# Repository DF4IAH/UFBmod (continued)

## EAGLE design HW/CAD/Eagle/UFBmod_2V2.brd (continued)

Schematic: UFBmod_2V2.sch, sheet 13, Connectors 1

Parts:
C1311: 1nF; C0402
C1321, C1381: 100nF; C0402
PF1311: 1.1A/2.2A; M1206
R1311: 330kR; R0402
R1321, R1331: 1kR; R0402
R1332, R1333, R1334, R1335, R1337, R1339, R1351, R1352, R1353, R1354, R1355, R1356, R1357, R1358, R1361, R1362, R1363, R1364, R1365, R1366: 100R; R0402
R1338: 10kR; R0402
R1381: 0R; R0402
R1382, R1383: NC; R0402
S1321: KSR223G_SMD_1POL
TP1371: TPB1,27; B1,27
X1311: MOLEX 105017-0001; USB-B-MICRO-SMD_MOLEX-105017-0001
X1331: XILINX-JTAG-14; 2X07_2MM00_SHROUDED_XILINX_JTAG
X1332: HEADER-1X2; 1X02
X1351, X1361: PHOENIX_1990067_1X8X2MM50_PTSA-0-5

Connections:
+2V5: R1382.2; also elsewhere on the board
+3V3: X1332.1; also elsewhere on the board
+5V_USB: PF1311.1; also elsewhere on the board
B2W_51: R1351.2, X1351.1
B2W_52: R1352.2, X1351.2
B2W_53: R1353.2, X1351.3
B2W_54: R1354.2, X1351.4
B2W_55: R1355.2, X1351.5
B2W_56: R1356.2, X1351.6
B2W_57: R1357.2, X1351.7
B2W_58: R1358.2, X1351.8
B2W_61: R1361.2, X1361.1
B2W_62: R1362.2, X1361.2
B2W_63: R1363.2, X1361.3
B2W_64: R1364.2, X1361.4
B2W_65: R1365.2, X1361.5
B2W_66: R1366.2, X1361.6
DDR3_INIT_CALIB_COMPLETE: TP1371.TP; also elsewhere on the board
FPGA_B16_L7_N: R1364.1; also elsewhere on the board
FPGA_B16_L7_P: R1363.1; also elsewhere on the board
FPGA_B16_L9_N: R1362.1; also elsewhere on the board
FPGA_B16_L9_P: R1361.1; also elsewhere on the board
FPGA_B16_L11_N: R1366.1; also elsewhere on the board
FPGA_B16_L11_P: R1365.1; also elsewhere on the board
FPGA_B16_L16_N: R1352.1; also elsewhere on the board
FPGA_B16_L16_P: R1351.1; also elsewhere on the board
FPGA_B16_L17_N: R1356.1; also elsewhere on the board
FPGA_B16_L17_P: R1355.1; also elsewhere on the board
FPGA_B16_L18_N: R1358.1; also elsewhere on the board
FPGA_B16_L18_P: R1357.1; also elsewhere on the board
FPGA_B16_L19_N: R1354.1; also elsewhere on the board
FPGA_B16_L19_P: R1353.1; also elsewhere on the board
FPGA_JTAGEN: R1339.2; also elsewhere on the board
FPGA_RESET: C1321.2, R1321.1; also elsewhere on the board
FPGA_RESET_R: R1321.2, S1321.1
FPGA_SRST: R1337.2; also elsewhere on the board
FPGA_TCK: R1333.2; also elsewhere on the board
FPGA_TDI: R1335.2; also elsewhere on the board
FPGA_TDO: R1334.2; also elsewhere on the board
FPGA_TMS: R1332.2; also elsewhere on the board
GND: C1311.1, C1321.1, C1381.1, R1311.1, R1338.2, X1311.GND, X1331.1, X1331.3, X1331.5, X1331.7, X1331.9, X1331.11, X1331.13, X1361.8; also elsewhere on the board
JC_SRST: R1337.1, X1331.14
JC_TCK: R1333.1, X1331.6
JC_TDI: R1335.1, X1331.10
JC_TDO: R1334.1, X1331.8
JC_TMS: R1332.1, X1331.4
JC_VCCO_0: R1331.1, X1331.2
JTAG_CPLD_EN: R1338.1, R1339.1, X1332.2
U1V8: R1383.2; also elsewhere on the board
U3V3: R1381.2; also elsewhere on the board
U3V3_JTAGREF: R1331.2; also elsewhere on the board
USB_D_N: X1311.D- (J_D-); also elsewhere on the board
USB_D_P: X1311.D+ (J_D+); also elsewhere on the board
USB_ID: X1311.ID (J_ID)
USB_SHIELD: C1311.2, R1311.2, X1311.JSHIELD (SHIELD), X1311.JSHIELD@2 (SHIELD), X1311.JSHIELD@3 (SHIELD), X1311.JSHIELD@4 (SHIELD), X1311.JSHIELD@5 (SHIELD), X1311.JSHIELD@6 (SHIELD)
USB_VBUS: PF1311.2, X1311.VBUS (J_VUSB)
VCCIO13: S1321.2 (S); also elsewhere on the board
VCCIO16: C1381.2, R1381.1, R1382.1, R1383.1; also elsewhere on the board
VIN_PWR: X1361.7; also elsewhere on the board

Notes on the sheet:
Connectors 1
Board-Wire-Connectors
LITTLEFUSE 1206L050YR
JTAG-Connector
USB-Connector
JTAG CPLD EN
Programmer: Digilent JTAG HS3
set to 3.3V
TI SN75240PWR

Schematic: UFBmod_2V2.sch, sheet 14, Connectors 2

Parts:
C1431, C1441: 1uF; C0402
C1432, C1442: 100nF; C0402
J1411: ABRACON_ARJE-0034; ARJE-0034_RJ45_WITH_MAGNETICS
R1421, R1422: 470R; R0402

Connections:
+3V3: C1431.1, C1432.1, C1441.1, C1442.1, J1411.5, J1411.6; also elsewhere on the board
ETH_DA_G: J1411.12, R1422.2
ETH_DA_Y: J1411.1, R1421.2
FPGA_ETH_DA_G: R1422.1; also elsewhere on the board
FPGA_ETH_DA_Y: R1421.1; also elsewhere on the board
FPGA_ETH_RD_N: J1411.8; also elsewhere on the board
FPGA_ETH_RD_P: J1411.7; also elsewhere on the board
FPGA_ETH_TD_N: J1411.4; also elsewhere on the board
FPGA_ETH_TD_P: J1411.3; also elsewhere on the board
GND: C1431.2, C1432.2, C1441.2, C1442.2, J1411.2, J1411.10, J1411.11, J1411.GND@11 (13), J1411.GND@12 (13), J1411.GND@21 (13), J1411.GND@22 (13); also elsewhere on the board

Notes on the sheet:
Connectors 2
Ethernet 100MBit Connector
TX+
TX-
RX+
RX-

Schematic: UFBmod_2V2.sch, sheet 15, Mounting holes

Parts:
H1511, H1512, H1513, H1514: MOUNT-PAD-ROUND3.2; 3,2-PAD

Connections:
GND: H1511.B3,2, H1512.B3,2, H1513.B3,2, H1514.B3,2; also elsewhere on the board

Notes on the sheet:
Mounting holes

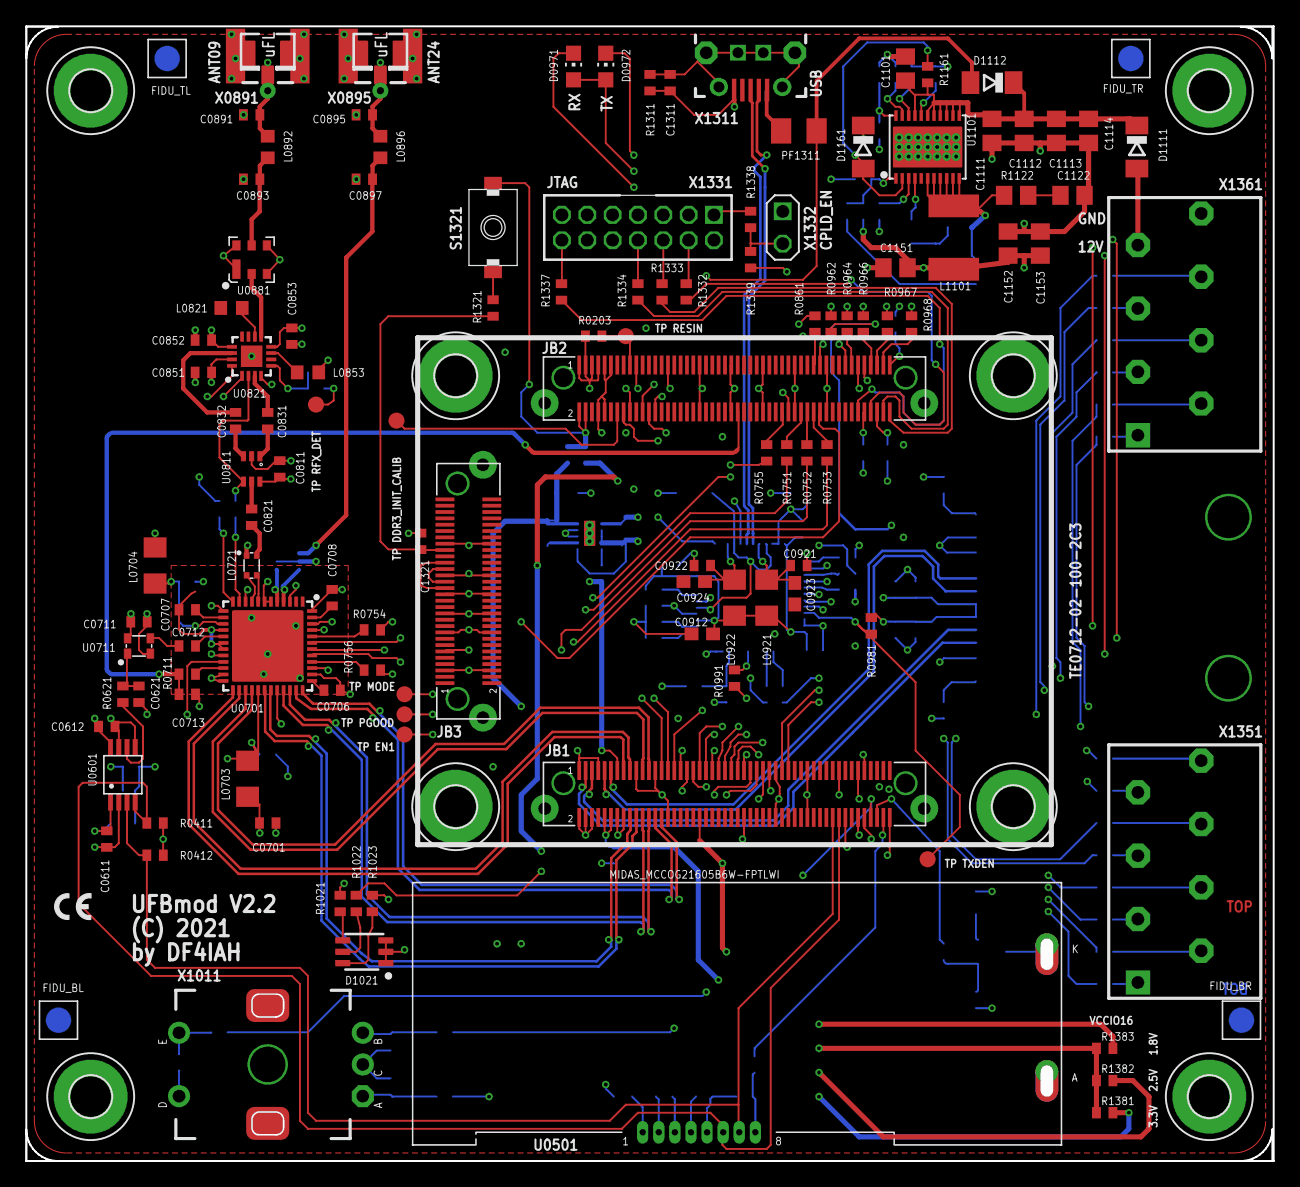
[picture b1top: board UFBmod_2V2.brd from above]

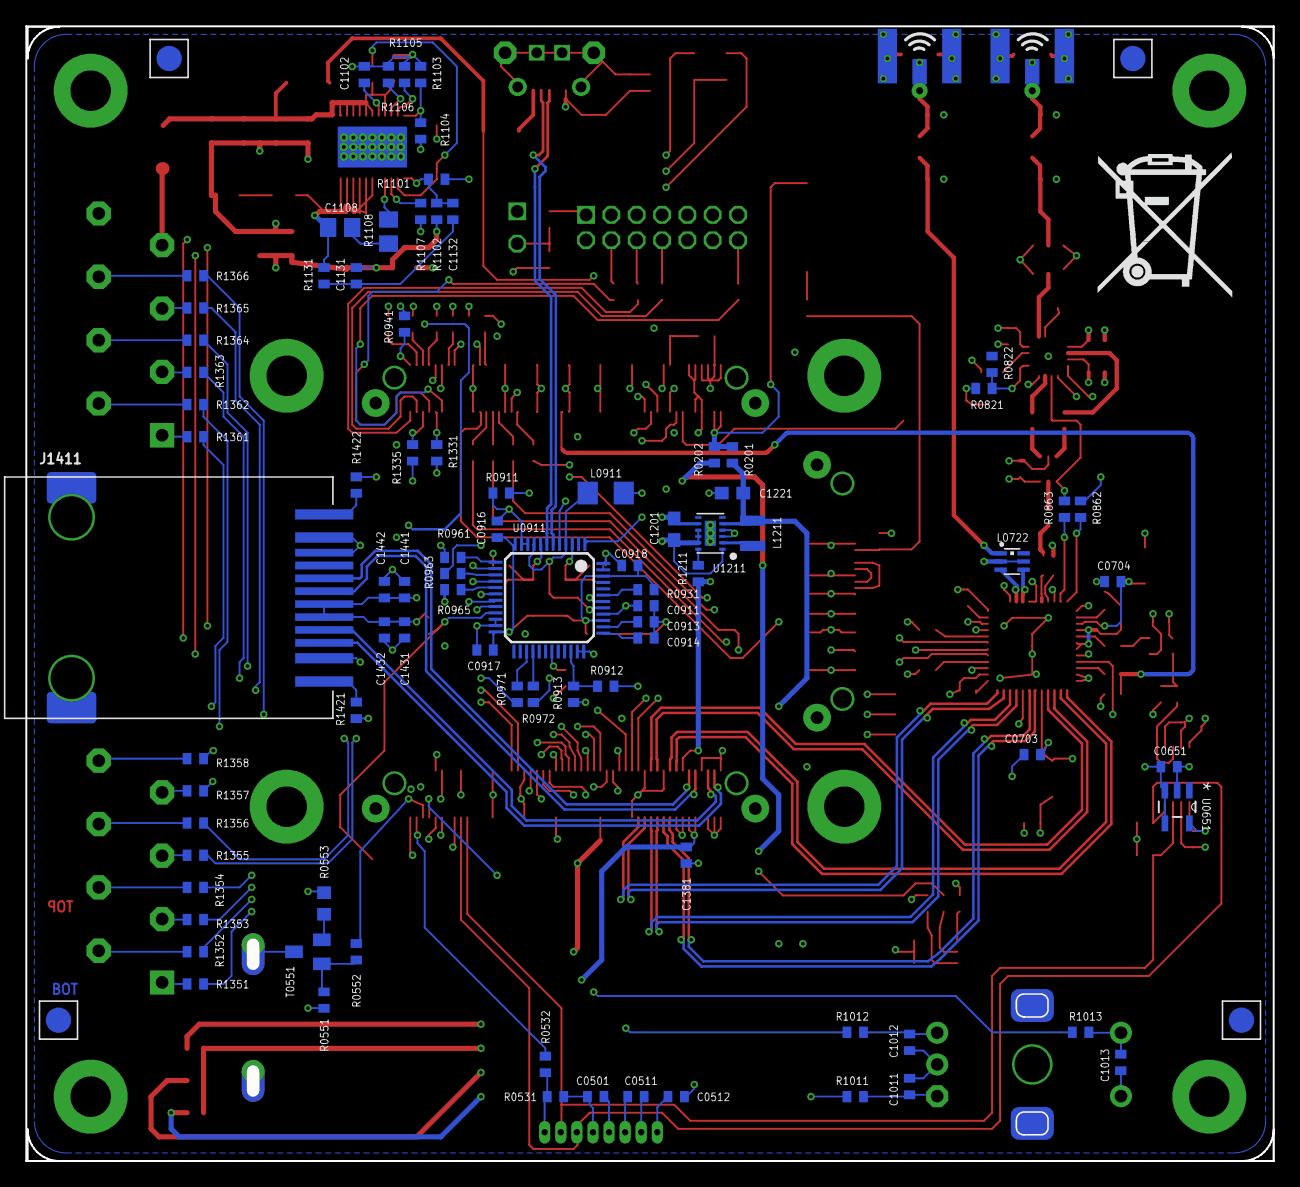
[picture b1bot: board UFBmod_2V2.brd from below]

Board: 6 copper layers, 97.6 x 88.7 mm, 214 parts (86 on the bottom side), 202 nets.

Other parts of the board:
FIDU_BL: FIDUCIAL_MARK_1MM
FIDU_BR: FIDUCIAL_MARK_1MM
FIDU_TL: FIDUCIAL_MARK_1MM
FIDU_TR: FIDUCIAL_MARK_1MM

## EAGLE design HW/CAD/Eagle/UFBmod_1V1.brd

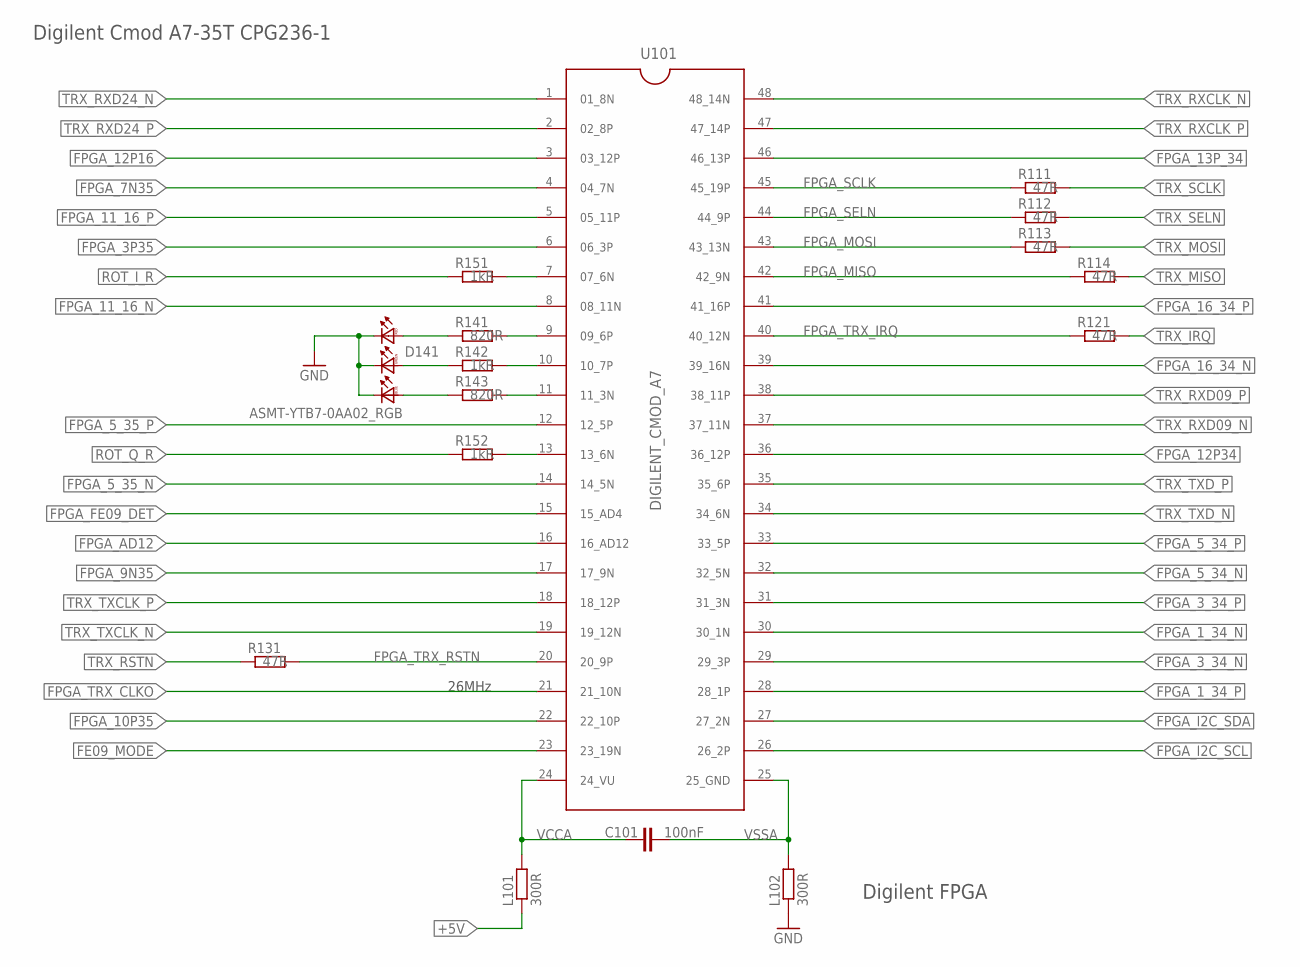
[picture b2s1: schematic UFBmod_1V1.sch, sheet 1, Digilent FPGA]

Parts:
C101: 100nF; C0402
D141: ASMT-YTB7-0AA02_RGB; ASMT-YTB7_0AA02_RGB
L101, L102: 300R; R1206
R111, R112, R113, R114, R121, R131: 47R; R0402
R141, R143: 820R; R0402
R142, R151, R152: 1kR; R0402
U101: DIGILENT_CMOD_A7; DIGILENT_CMOD_A7__DIP48

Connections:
+5V: L101.1; also elsewhere on the board
FE09_MODE: U101.23 (23_19N); also elsewhere on the board
FPGA_1_34_N: U101.30 (30_1N); also elsewhere on the board
FPGA_1_34_P: U101.28 (28_1P); also elsewhere on the board
FPGA_3P35: U101.6 (06_3P); also elsewhere on the board
FPGA_3_34_N: U101.29 (29_3P); also elsewhere on the board
FPGA_3_34_P: U101.31 (31_3N); also elsewhere on the board
FPGA_5_34_N: U101.32 (32_5N); also elsewhere on the board
FPGA_5_34_P: U101.33 (33_5P); also elsewhere on the board
FPGA_5_35_N: U101.14 (14_5N); also elsewhere on the board
FPGA_5_35_P: U101.12 (12_5P); also elsewhere on the board
FPGA_7N35: U101.4 (04_7N); also elsewhere on the board
FPGA_9N35: U101.17 (17_9N); also elsewhere on the board
FPGA_10P35: U101.22 (22_10P); also elsewhere on the board
FPGA_11_16_N: U101.8 (08_11N); also elsewhere on the board
FPGA_11_16_P: U101.5 (05_11P); also elsewhere on the board
FPGA_12P16: U101.3 (03_12P); also elsewhere on the board
FPGA_12P34: U101.36 (36_12P); also elsewhere on the board
FPGA_13P_34: U101.46 (46_13P); also elsewhere on the board
FPGA_16_34_N: U101.39 (39_16N); also elsewhere on the board
FPGA_16_34_P: U101.41 (41_16P); also elsewhere on the board
FPGA_AD12: U101.16 (16_AD12); also elsewhere on the board
FPGA_FE09_DET: U101.15 (15_AD4); also elsewhere on the board
FPGA_I2C_SCL: U101.26 (26_2P); also elsewhere on the board
FPGA_I2C_SDA: U101.27 (27_2N); also elsewhere on the board
FPGA_MISO: R114.1, U101.42 (42_9N)
FPGA_MOSI: R113.1, U101.43 (43_13N)
FPGA_SCLK: R111.1, U101.45 (45_19P)
FPGA_SELN: R112.1, U101.44 (44_9P)
FPGA_TRX_CLKO: U101.21 (21_10N); also elsewhere on the board
FPGA_TRX_IRQ: R121.1, U101.40 (40_12N)
FPGA_TRX_RSTN: R131.2, U101.20 (20_9P)
GND: D141.1 (BC), D141.2 (GC), D141.3 (RC), L102.1; also elsewhere on the board
LED_B: R143.2, U101.11 (11_3N)
LED_B_R: D141.6 (BA), R143.1
LED_G: R142.2, U101.10 (10_7P)
LED_G_R: D141.5 (GA), R142.1
LED_R: R141.2, U101.9 (09_6P)
LED_R_R: D141.4 (RA), R141.1
ROT_I: R151.2, U101.7 (07_6N)
ROT_I_R: R151.1; also elsewhere on the board
ROT_Q: R152.2, U101.13 (13_6N)
ROT_Q_R: R152.1; also elsewhere on the board
TRX_IRQ: R121.2; also elsewhere on the board
TRX_MISO: R114.2; also elsewhere on the board
TRX_MOSI: R113.2; also elsewhere on the board
TRX_RSTN: R131.1; also elsewhere on the board
TRX_RXCLK_N: U101.48 (48_14N); also elsewhere on the board
TRX_RXCLK_P: U101.47 (47_14P); also elsewhere on the board
TRX_RXD09_N: U101.37 (37_11N); also elsewhere on the board
TRX_RXD09_P: U101.38 (38_11P); also elsewhere on the board
TRX_RXD24_N: U101.1 (01_8N); also elsewhere on the board
TRX_RXD24_P: U101.2 (02_8P); also elsewhere on the board
TRX_SCLK: R111.2; also elsewhere on the board
TRX_SELN: R112.2; also elsewhere on the board
TRX_TXCLK_N: U101.19 (19_12N); also elsewhere on the board
TRX_TXCLK_P: U101.18 (18_12P); also elsewhere on the board
TRX_TXD_N: U101.34 (34_6N); also elsewhere on the board
TRX_TXD_P: U101.35 (35_6P); also elsewhere on the board
VCCA: C101.2, L101.2, U101.24 (24_VU)
VSSA: C101.1, L102.2, U101.25 (25_GND)

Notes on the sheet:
Digilent FPGA
Digilent Cmod A7-35T CPG236-1
26MHz

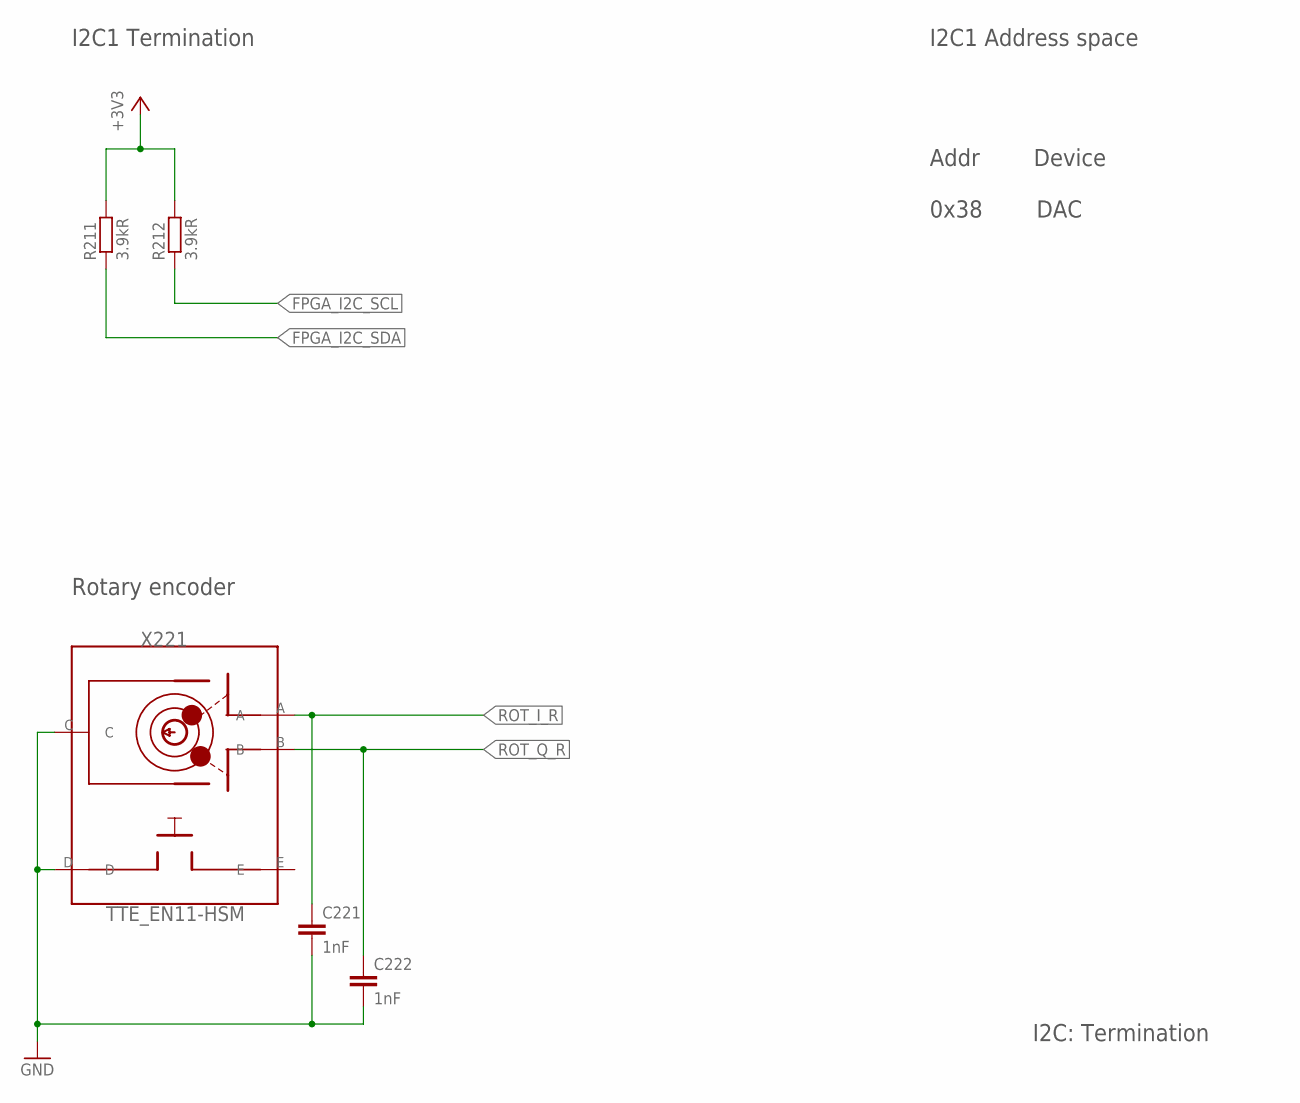
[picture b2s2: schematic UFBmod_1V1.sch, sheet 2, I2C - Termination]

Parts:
C221, C222: 1nF; C0402
R211, R212: 3.9kR; R0402
X221: TTE_EN11-HSM

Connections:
+3V3: R211.2, R212.2; also elsewhere on the board
FPGA_I2C_SCL: R212.1; also elsewhere on the board
FPGA_I2C_SDA: R211.1; also elsewhere on the board
GND: C221.2, C222.2, X221.C, X221.D; also elsewhere on the board
ROT_I_R: C221.1, X221.A; also elsewhere on the board
ROT_Q_R: C222.1, X221.B; also elsewhere on the board

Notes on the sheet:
I2C: Termination
Addr Device 0x38 DAC
I2C1 Termination
I2C1 Address space
Rotary encoder

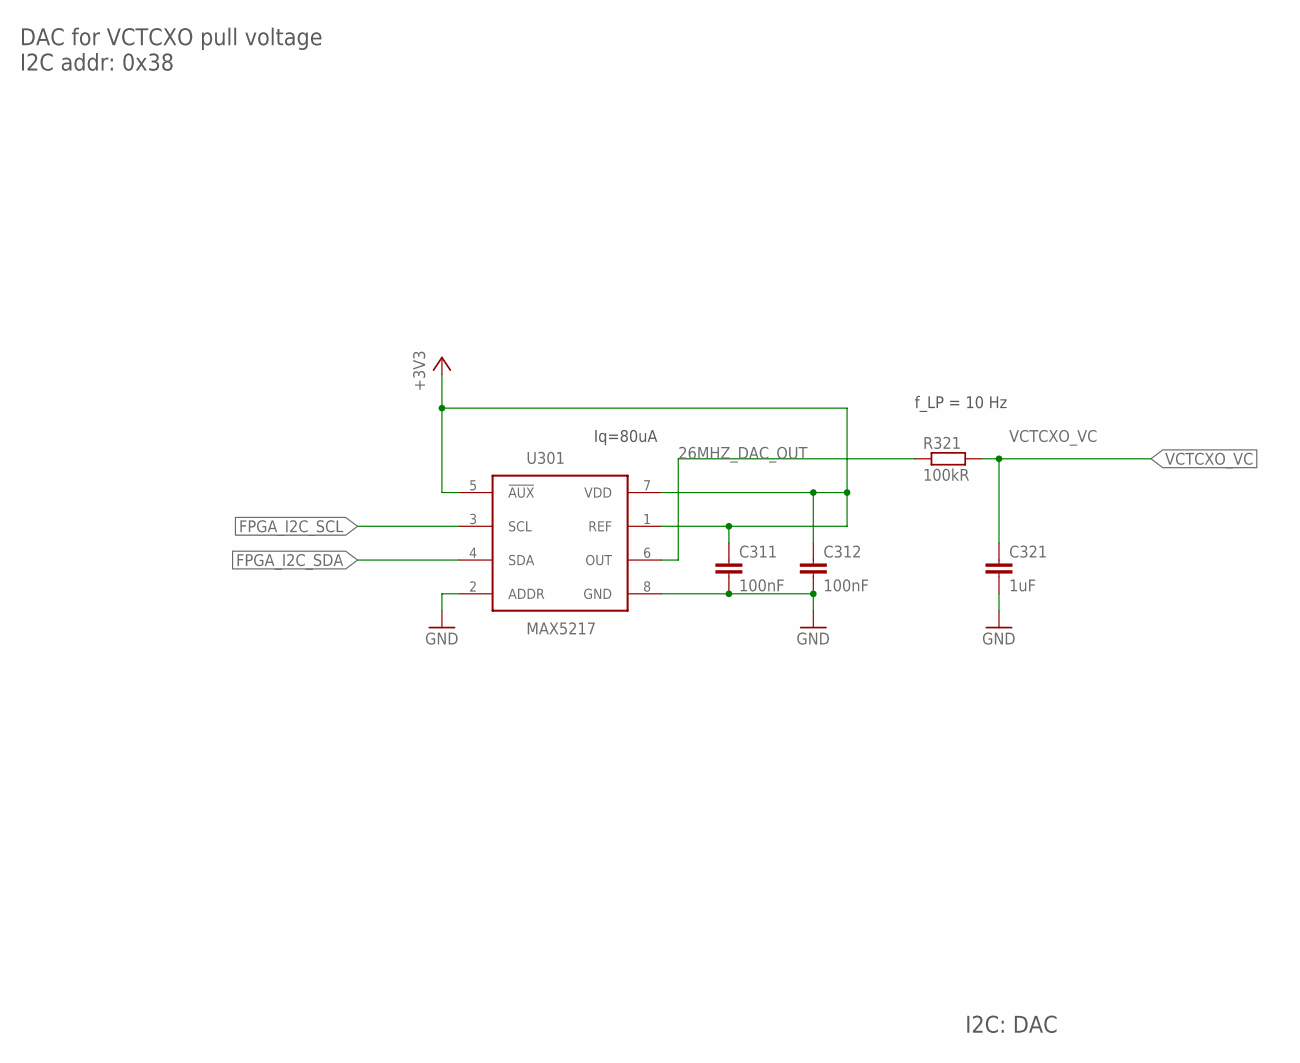
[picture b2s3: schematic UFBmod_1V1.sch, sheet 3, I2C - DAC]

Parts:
C311, C312: 100nF; C0402
C321: 1uF; C0402
R321: 100kR; R0402
U301: MAX5217; µMAX8

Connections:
26MHZ_DAC_OUT: R321.1, U301.6 (OUT)
+3V3: C311.1, C312.1, U301.1 (REF), U301.5 (!AUX), U301.7 (VDD); also elsewhere on the board
FPGA_I2C_SCL: U301.3 (SCL); also elsewhere on the board
FPGA_I2C_SDA: U301.4 (SDA); also elsewhere on the board
GND: C311.2, C312.2, C321.2, U301.2 (ADDR), U301.8 (GND); also elsewhere on the board
VCTCXO_VC: C321.1, R321.2; also elsewhere on the board

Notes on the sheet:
f_LP = 10 Hz
Iq=80uA
DAC for VCTCXO pull voltage I2C addr: 0x38
I2C: DAC

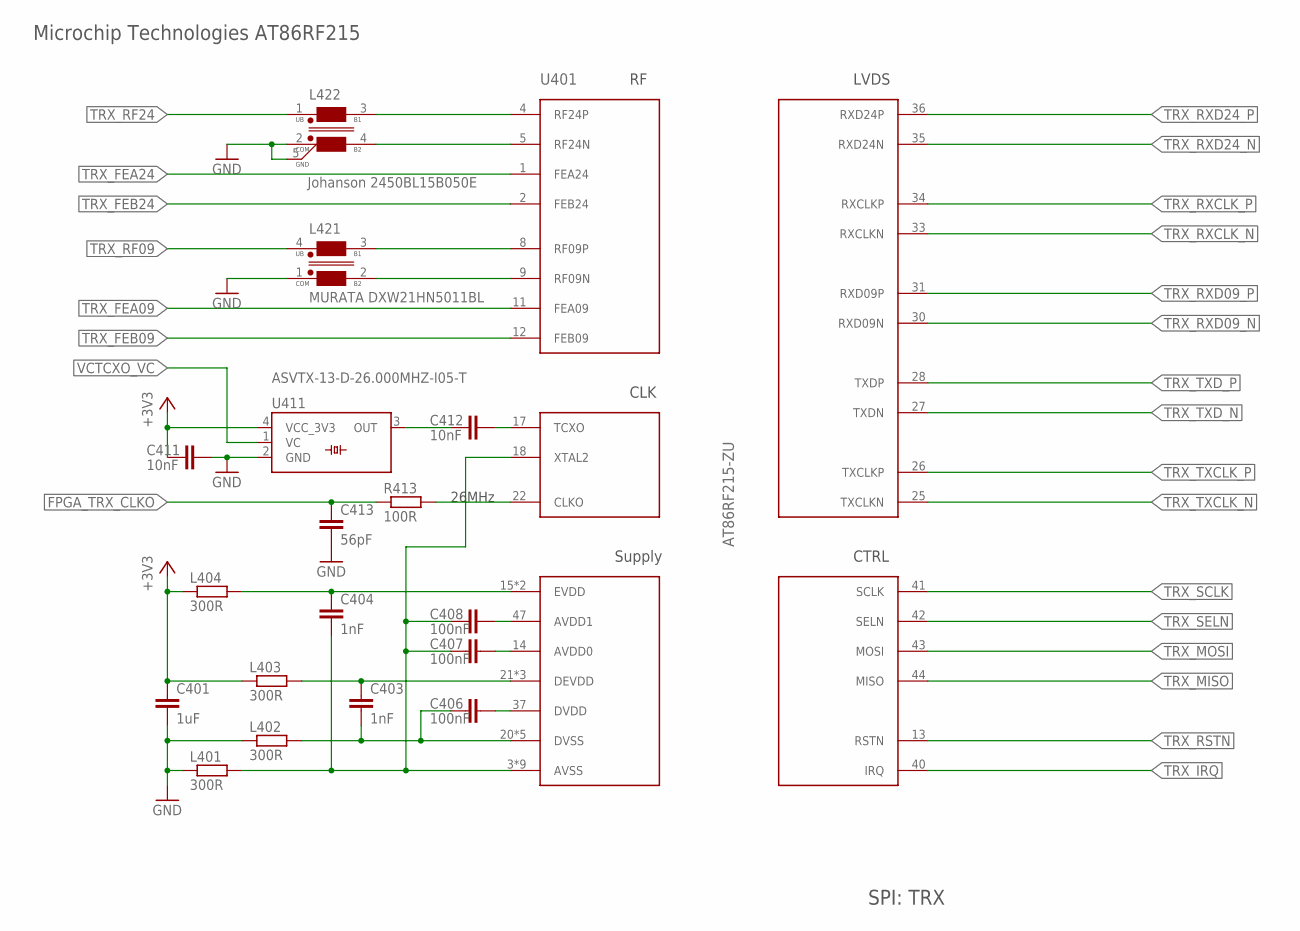
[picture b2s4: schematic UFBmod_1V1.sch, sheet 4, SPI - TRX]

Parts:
C401: 1uF; C0402
C403, C404: 1nF; C0402
C406, C407, C408: 100nF; C0402
C411, C412: 10nF; C0402
C413: 56pF; C0402
L401, L402, L403, L404: 300R; R1206
L421: MURATA DXW21HN5011BL; DXW21HN5011BL
L422: Johanson 2450BL15B050E; 2450BL15B050
R413: 100R; R0402
U401: AT86RF215-ZU; QFN48_7X7-0P5-PAD
U411: ASVTX-13-D-26.000MHZ-I05-T; ASVTX-13

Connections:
+3V3: C401.1, C411.1, L403.1, L404.1, U411.4 (VCC_3V3); also elsewhere on the board
FPGA_TRX_CLKO: C413.1, R413.1; also elsewhere on the board
GND: C401.2, C411.2, C413.2, L401.1, L402.1, L421.1 (COM), L422.2 (COM), L422.5 (G_N_D), U411.2 (GND); also elsewhere on the board
TRX_AVDD0: C407.2, U401.14 (AVDD0)
TRX_AVDD1: C408.2, U401.47 (AVDD1)
TRX_AVSS: C404.2, C407.1, C408.1, L401.2, U401.3 (AVSS), U401.6 (AVSS), U401.7 (AVSS), U401.10 (AVSS), U401.16 (AVSS), U401.18 (XTAL2), U401.19 (AVSS), U401.45 (AVSS), U401.48 (AVSS), U401.49 (AVSS)
TRX_CLKO: R413.2, U401.22 (CLKO)
TRX_DEVDD: C403.1, L403.2, U401.21 (DEVDD), U401.29 (DEVDD), U401.39 (DEVDD)
TRX_DVDD: C406.2, U401.37 (DVDD)
TRX_DVSS: C403.2, C406.1, L402.2, U401.20 (DVSS), U401.23 (DVSS), U401.24 (DVSS), U401.32 (DVSS), U401.38 (DVSS)
TRX_EVDD: C404.1, L404.2, U401.15 (EVDD), U401.46 (EVDD)
TRX_FEA09: U401.11 (FEA09); also elsewhere on the board
TRX_FEA24: U401.1 (FEA24)
TRX_FEB09: U401.12 (FEB09); also elsewhere on the board
TRX_FEB24: U401.2 (FEB24)
TRX_IRQ: U401.40 (IRQ); also elsewhere on the board
TRX_MISO: U401.44 (MISO); also elsewhere on the board
TRX_MOSI: U401.43 (MOSI); also elsewhere on the board
TRX_RF09: L421.4 (UB); also elsewhere on the board
TRX_RF09_N: L421.2 (B2), U401.9 (RF09N)
TRX_RF09_P: L421.3 (B1), U401.8 (RF09P)
TRX_RF24: L422.1 (UB); also elsewhere on the board
TRX_RF24_N: L422.4 (B2), U401.5 (RF24N)
TRX_RF24_P: L422.3 (B1), U401.4 (RF24P)
TRX_RSTN: U401.13 (RSTN); also elsewhere on the board
TRX_RXCLK_N: U401.33 (RXCLKN); also elsewhere on the board
TRX_RXCLK_P: U401.34 (RXCLKP); also elsewhere on the board
TRX_RXD09_N: U401.30 (RXD09N); also elsewhere on the board
TRX_RXD09_P: U401.31 (RXD09P); also elsewhere on the board
TRX_RXD24_N: U401.35 (RXD24N); also elsewhere on the board
TRX_RXD24_P: U401.36 (RXD24P); also elsewhere on the board
TRX_SCLK: U401.41 (SCLK); also elsewhere on the board
TRX_SELN: U401.42 (SELN); also elsewhere on the board
TRX_TCXO: C412.2, U401.17 (TCXO)
TRX_TXCLK_N: U401.25 (TXCLKN); also elsewhere on the board
TRX_TXCLK_P: U401.26 (TXCLKP); also elsewhere on the board
TRX_TXD_N: U401.27 (TXDN); also elsewhere on the board
TRX_TXD_P: U401.28 (TXDP); also elsewhere on the board
VCTCXO_OUT: C412.1, U411.3 (OUT)
VCTCXO_VC: U411.1 (VC); also elsewhere on the board

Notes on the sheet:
SPI: TRX
Microchip Technologies AT86RF215
26MHz

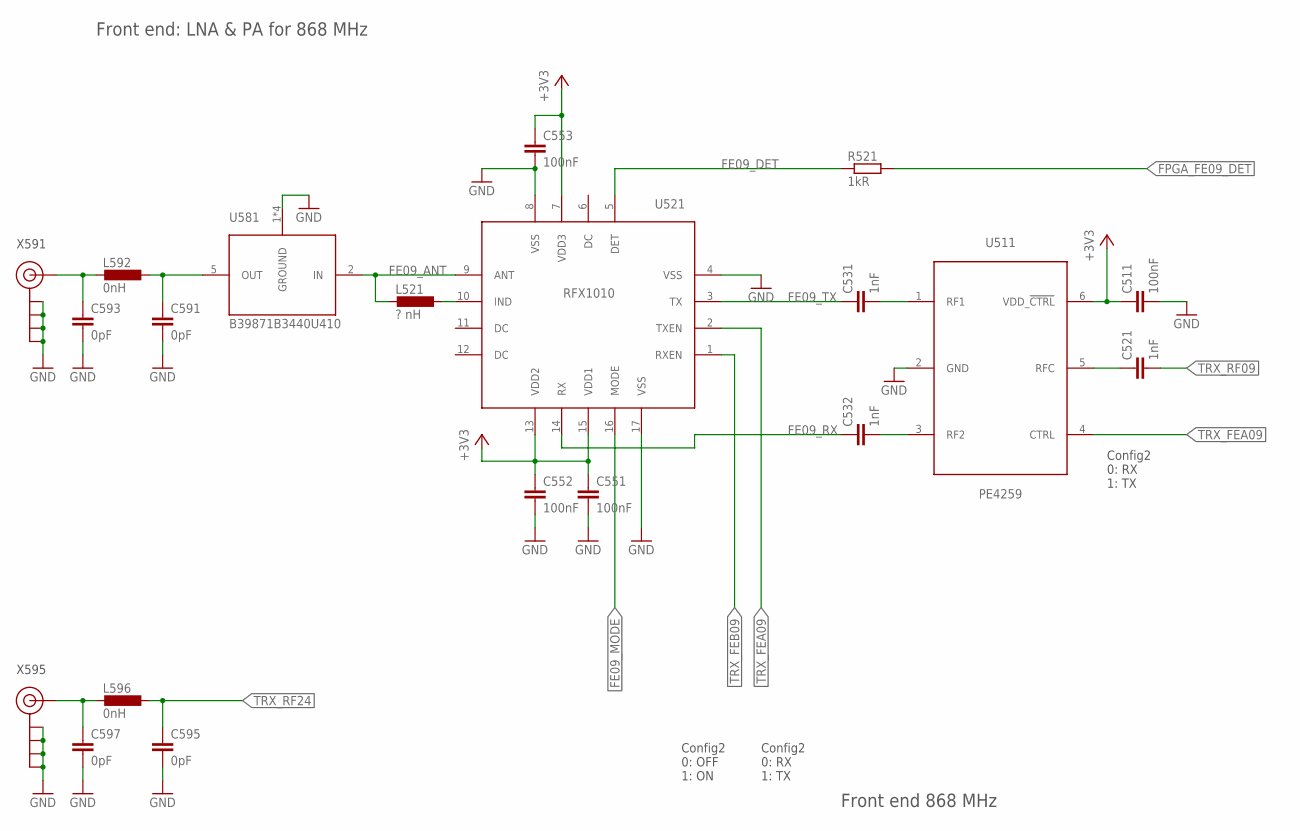
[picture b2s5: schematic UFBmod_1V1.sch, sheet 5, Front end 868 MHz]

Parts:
C511, C551, C552, C553: 100nF; C0402
C521, C531, C532: 1nF; C0402
C591, C593, C595, C597: 0pF; C0402
L521: ? nH; L0603
L592, L596: 0nH; L0603
R521: 1kR; R0402
U511: PE4259; SC-70_6-LEAD_2X1MM25_0P65
U521: RFX1010; QFN16-3X3-0P5-PAD
U581: B39871B3440U410; B3440_3MM-X-3MM
X591, X595: ANTENNATINY; SMA_UFL_PAD_TINY

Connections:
+3V3: C511.1, C551.1, C552.1, C553.1, U511.6 (VDD_!CTRL), U521.7 (VDD3), U521.13 (VDD2), U521.15 (VDD1); also elsewhere on the board
ANT09: C593.1, L592.2, X591.ANT1 (SIGNAL), X591.ANT2 (SIGNAL), X591.ANT3 (SIGNAL)
ANT09_MATCH: C591.1, L592.1, U581.5 (OUT)
ANT24: C597.1, L596.2, X595.ANT1 (SIGNAL), X595.ANT2 (SIGNAL), X595.ANT3 (SIGNAL)
FE09_ANT: L521.2, U521.9 (ANT), U581.2 (IN)
FE09_DET: R521.1, U521.5 (DET)
FE09_IND: L521.1, U521.10 (IND)
FE09_MODE: U521.16 (MODE); also elsewhere on the board
FE09_RX: C532.1, U521.14 (RX)
FE09_TX: C531.1, U521.3 (TX)
FPGA_FE09_DET: R521.2; also elsewhere on the board
GND: C511.2, C551.2, C552.2, C553.2, C591.2, C593.2, C595.2, C597.2, U511.2 (GND), U521.4 (VSS), U521.8 (VSS), U521.17 (VSS), U581.1 (GROUND), U581.3 (GROUND), U581.4 (GROUND), U581.6 (GROUND), X591.GND1 (GND), X591.GND2 (GND), X591.GND3 (GND), X591.GND4 (GND), X595.GND1 (GND), X595.GND2 (GND), X595.GND3 (GND), X595.GND4 (GND); also elsewhere on the board
PE09_RF1: C531.2, U511.1 (RF1)
PE09_RF2: C532.2, U511.3 (RF2)
PE09_RFC: C521.1, U511.5 (RFC)
TRX_FEA09: U511.4 (CTRL), U521.2 (TXEN); also elsewhere on the board
TRX_FEB09: U521.1 (RXEN); also elsewhere on the board
TRX_RF09: C521.2; also elsewhere on the board
TRX_RF24: C595.1, L596.1; also elsewhere on the board

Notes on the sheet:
Front end: LNA & PA for 868 MHz
Front end 868 MHz
Config2 0: RX 1: TX
Config2 0: OFF 1: ON
X591
X595

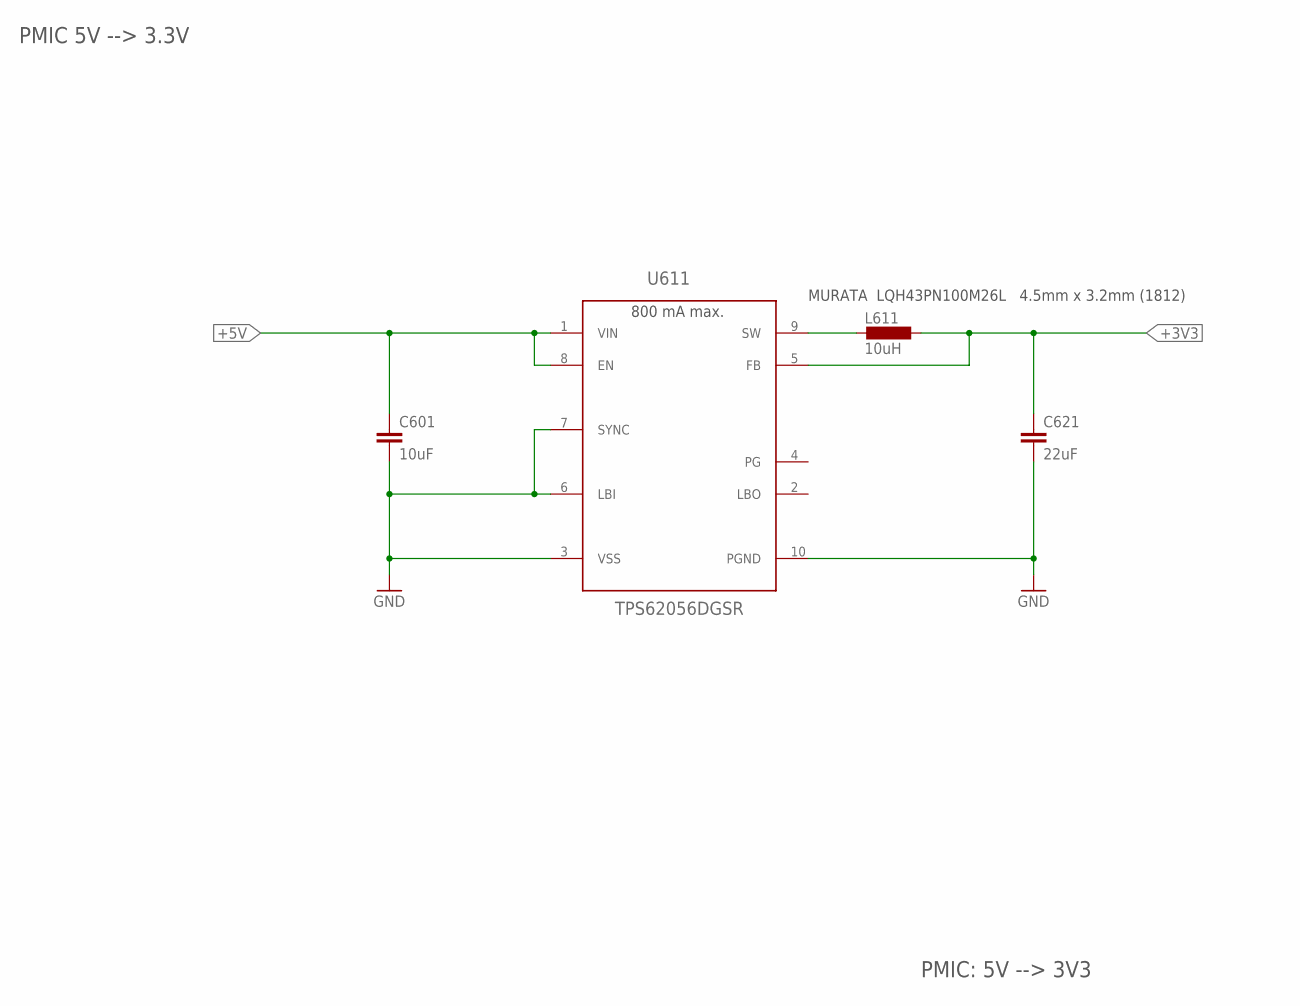
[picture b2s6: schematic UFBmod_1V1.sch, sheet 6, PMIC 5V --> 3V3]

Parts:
C601: 10uF; C0603
C621: 22uF; C0603
L611: 10uH; L1812
U611: TPS62056DGSR; S-PDSO-G10

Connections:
+3V3: C621.1, L611.1, U611.5 (FB); also elsewhere on the board
+5V: C601.1, U611.1 (VIN), U611.8 (EN); also elsewhere on the board
GND: C601.2, C621.2, U611.3 (VSS), U611.6 (LBI), U611.7 (SYNC), U611.10 (PGND); also elsewhere on the board
PMIC3V3_SW: L611.2, U611.9 (SW)

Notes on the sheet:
PMIC 5V --> 3.3V
PMIC: 5V --> 3V3
800 mA max.
MURATA LQH43PN100M26L 4.5mm x 3.2mm (1812)

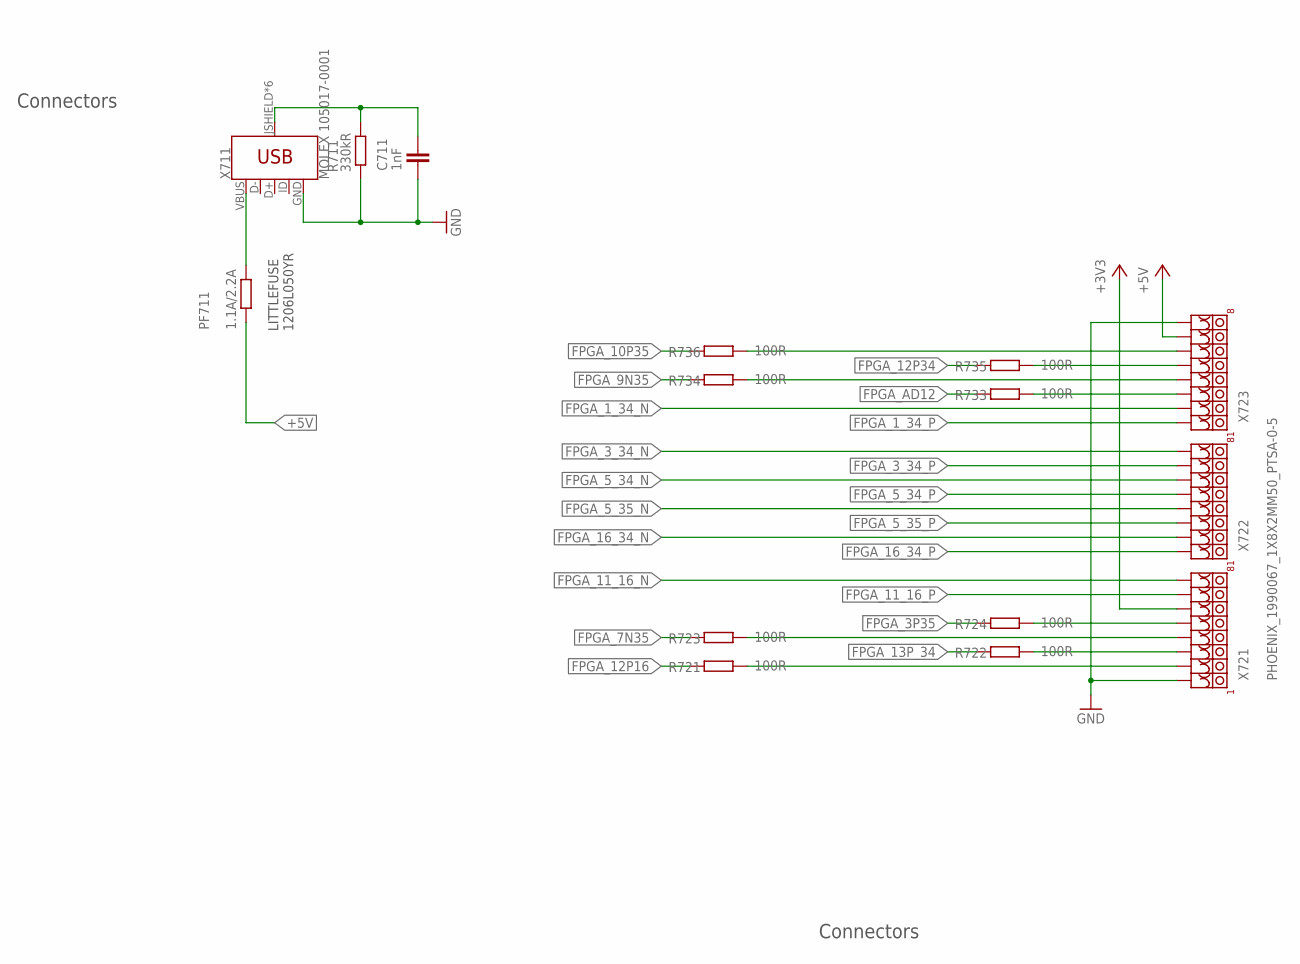
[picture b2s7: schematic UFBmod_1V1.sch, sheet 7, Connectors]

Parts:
C711: 1nF; C0402
PF711: 1.1A/2.2A; M1206
R711: 330kR; R0402
R721, R722, R723, R724, R733, R734, R735, R736: 100R; R0402
X711: MOLEX 105017-0001; USB-B-MICRO-SMD_MOLEX-105017-0001
X721, X722, X723: PHOENIX_1990067_1X8X2MM50_PTSA-0-5

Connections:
+3V3: X721.6; also elsewhere on the board
+5V: PF711.1, X723.7; also elsewhere on the board
FPGA_1_34_N: X723.2; also elsewhere on the board
FPGA_1_34_P: X723.1; also elsewhere on the board
FPGA_3P35: R724.1; also elsewhere on the board
FPGA_3P35_R: R724.2, X721.5
FPGA_3_34_N: X722.8; also elsewhere on the board
FPGA_3_34_P: X722.7; also elsewhere on the board
FPGA_5_34_N: X722.6; also elsewhere on the board
FPGA_5_34_P: X722.5; also elsewhere on the board
FPGA_5_35_N: X722.4; also elsewhere on the board
FPGA_5_35_P: X722.3; also elsewhere on the board
FPGA_7N35: R723.1; also elsewhere on the board
FPGA_7N35_R: R723.2, X721.4
FPGA_9N35: R734.1; also elsewhere on the board
FPGA_9N35_R: R734.2, X723.4
FPGA_10P35: R736.1; also elsewhere on the board
FPGA_10P35_R: R736.2, X723.6
FPGA_11_16_N: X721.8; also elsewhere on the board
FPGA_11_16_P: X721.7; also elsewhere on the board
FPGA_12P16: R721.1; also elsewhere on the board
FPGA_12P16_R: R721.2, X721.2
FPGA_12P34: R735.1; also elsewhere on the board
FPGA_12P34_R: R735.2, X723.5
FPGA_13P_34: R722.1; also elsewhere on the board
FPGA_13P_34_R: R722.2, X721.3
FPGA_16_34_N: X722.2; also elsewhere on the board
FPGA_16_34_P: X722.1; also elsewhere on the board
FPGA_AD12: R733.1; also elsewhere on the board
FPGA_AD12_R: R733.2, X723.3
GND: C711.1, R711.1, X711.GND, X721.1, X723.8; also elsewhere on the board
USB_SHIELD: C711.2, R711.2, X711.JSHIELD (SHIELD), X711.JSHIELD@2 (SHIELD), X711.JSHIELD@3 (SHIELD), X711.JSHIELD@4 (SHIELD), X711.JSHIELD@5 (SHIELD), X711.JSHIELD@6 (SHIELD)
USB_VBUS: PF711.2, X711.VBUS (J_VUSB)

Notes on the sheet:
Connectors
LITTLEFUSE 1206L050YR
